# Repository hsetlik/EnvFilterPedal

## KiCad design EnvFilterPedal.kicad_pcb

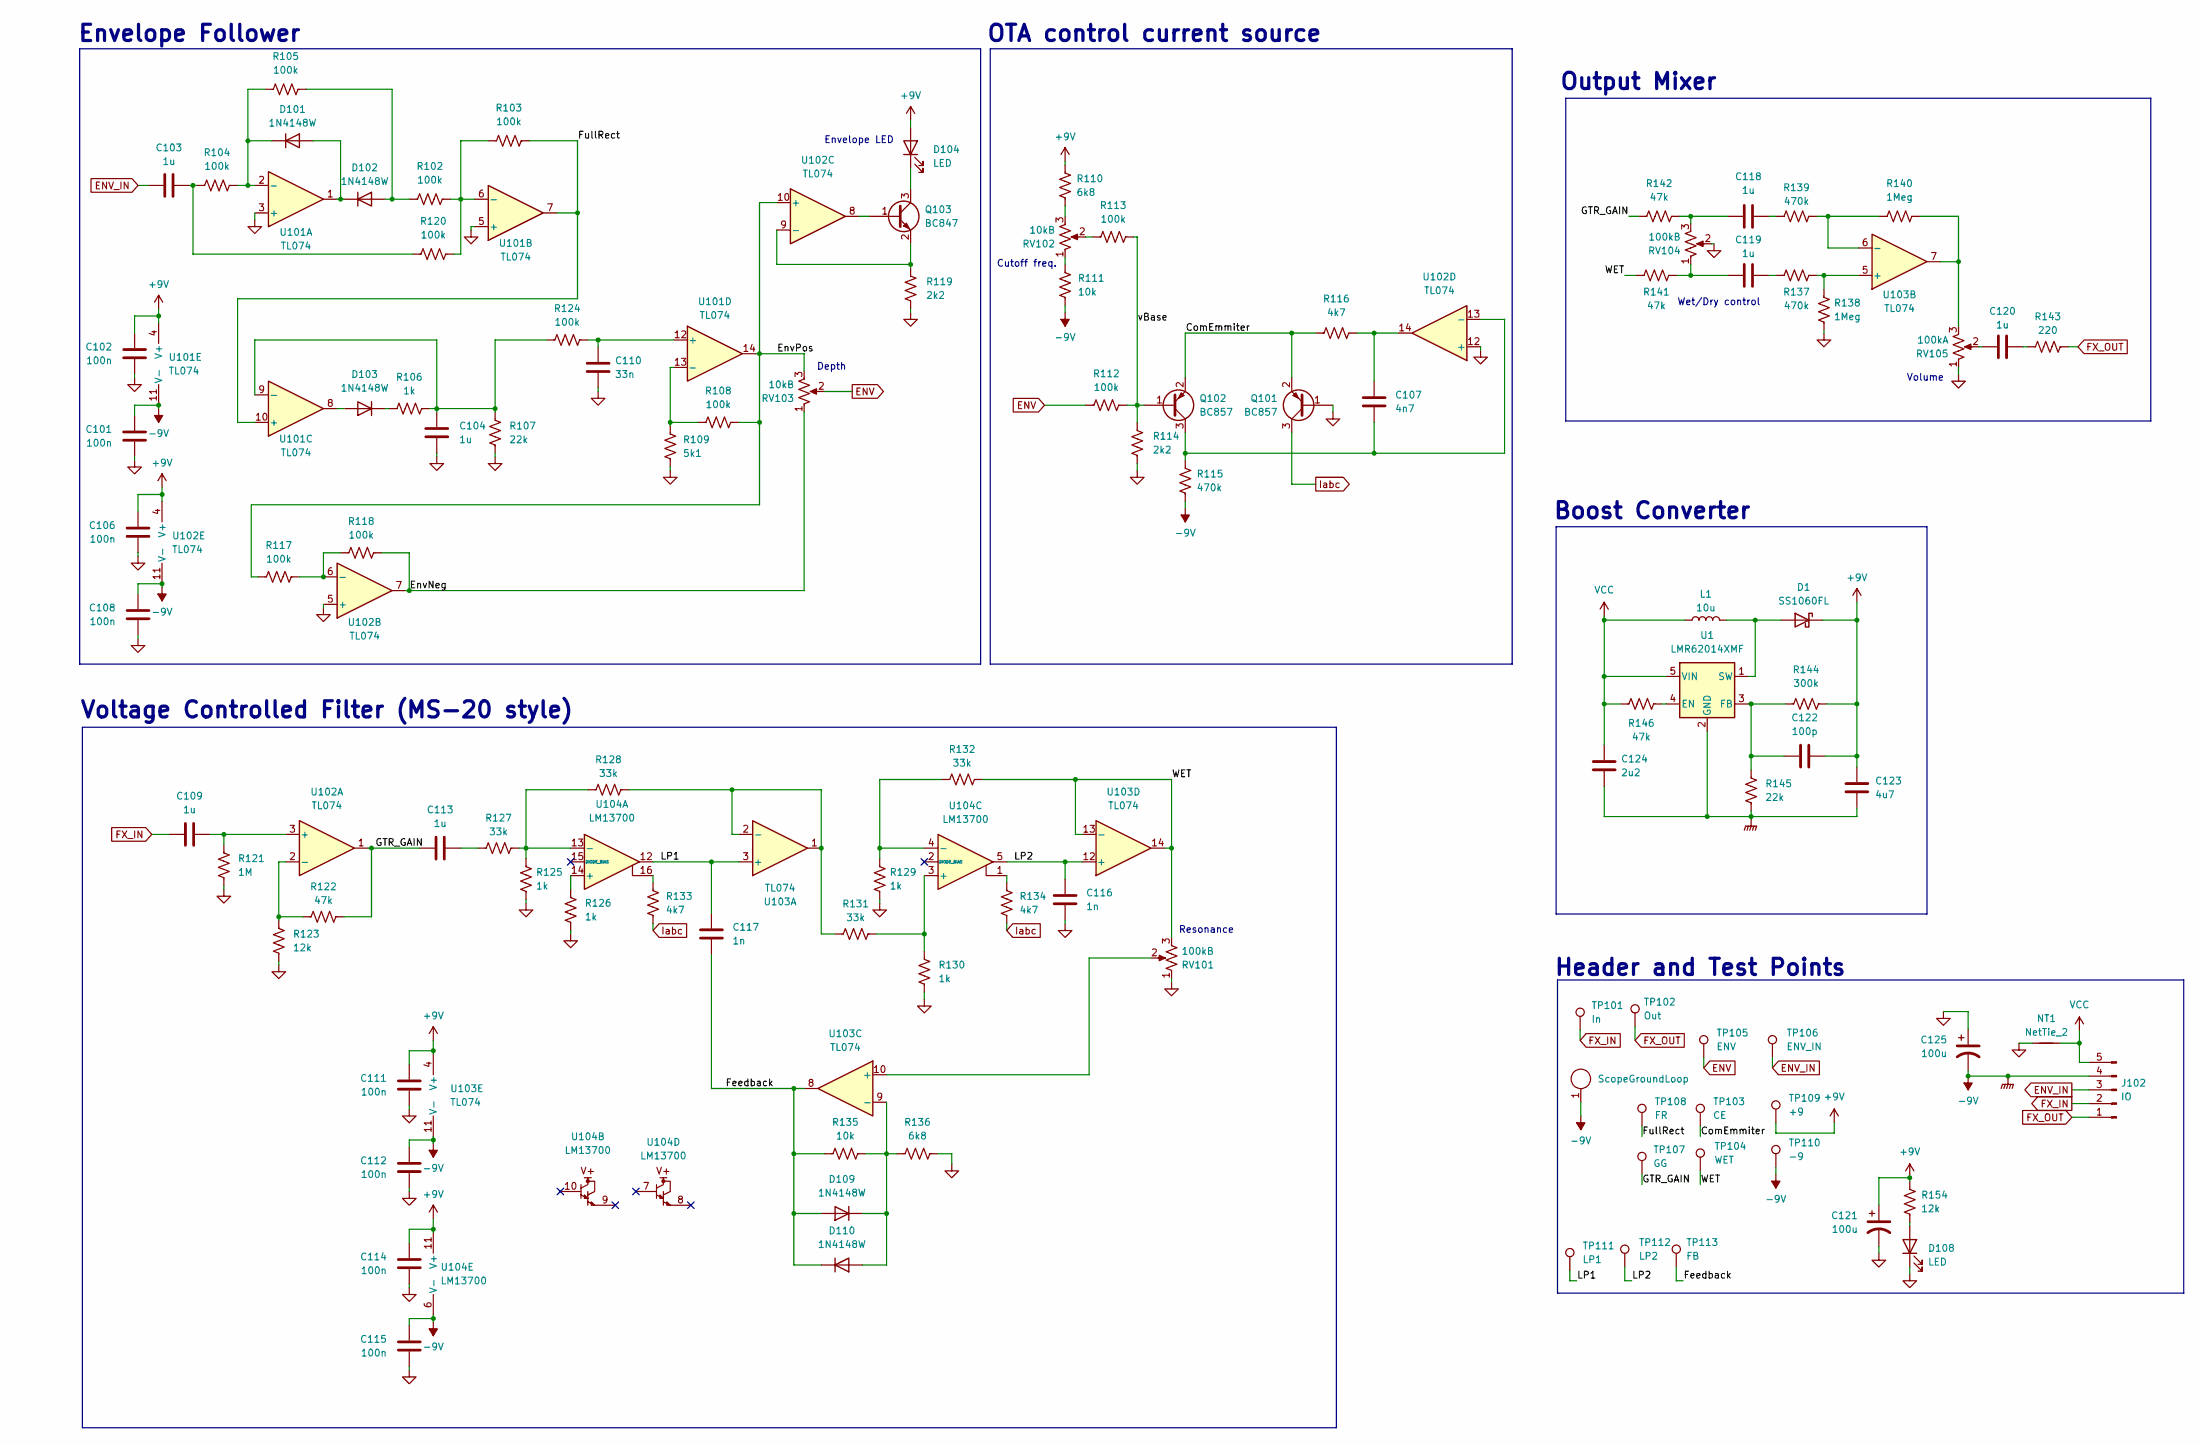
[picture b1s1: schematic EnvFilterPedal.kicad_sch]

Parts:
C101, C102, C106, C108, C111, C112, C114, C115: 100n; C_0805_2012Metric
C103, C104, C109, C113, C118, C119, C120: 1u; C_0805_2012Metric
C107: 4n7; C_0805_2012Metric
C110: 33n; C_0805_2012Metric
C116, C117: 1n; C_0805_2012Metric
C121, C125: 100u; CP_Radial_D5.0mm_P2.00mm
C122: 100p; C_0805_2012Metric
C123: 4u7; C_0805_2012Metric
C124: 2u2; C_0805_2012Metric
D1: SS1060FL; D_SOD-123F
D101, D102, D103, D109, D110: 1N4148W; D_SOD-123
D104, D108: LED; LED_D3.0mm
J101: ScopeGroundLoop; THT_GND_WIRE
J102: IO; PinHeader_1x05_P2.54mm_Vertical
L1: 10u; L_SigTransformer_SLPPI04_15
NT1: NetTie_2; NetTie-2_SMD_Pad0.5mm
Q101, Q102: BC857; SOT-23
Q103: BC847; SOT-23
R102, R103, R104, R105, R108, R112, R113, R117, R118, R120, R124: 100k; R_0805_2012Metric
R106, R125, R126, R129, R130: 1k; R_0805_2012Metric
R107, R145: 22k; R_0805_2012Metric
R109: 5k1; R_0805_2012Metric
R110, R136: 6k8; R_0805_2012Metric
R111, R135: 10k; R_0805_2012Metric
R114, R119: 2k2; R_0805_2012Metric
R115, R137, R139: 470k; R_0805_2012Metric
R116, R133, R134: 4k7; R_0805_2012Metric
R121: 1M; R_0805_2012Metric
R122, R141, R142, R146: 47k; R_0805_2012Metric
R123, R154: 12k; R_0805_2012Metric
R127, R128, R131, R132: 33k; R_0805_2012Metric
R138, R140: 1Meg; R_0805_2012Metric
R143: 220; R_0805_2012Metric
R144: 300k; R_0805_2012Metric
RV101, RV104: 100kB; Potentiometer_Alpha_RV16AF_42_VeryLong
RV102, RV103: 10kB; Potentiometer_Alpha_RV16AF_42_VeryLong
RV105: 100kA; Potentiometer_Alpha_RV16AF_42_VeryLong
TP101: In; TestPoint_THTPad_D2.0mm_Drill1.0mm_VAL
TP102: Out; TestPoint_THTPad_D2.0mm_Drill1.0mm_VAL
TP103: CE; TestPoint_THTPad_D2.0mm_Drill1.0mm_VAL
TP104: WET; TestPoint_THTPad_D2.0mm_Drill1.0mm_VAL
TP105: ENV; TestPoint_THTPad_D2.0mm_Drill1.0mm_VAL
TP106: ENV_IN; TestPoint_THTPad_D2.0mm_Drill1.0mm_VAL
TP107: GG; TestPoint_THTPad_D2.0mm_Drill1.0mm_VAL
TP108: FR; TestPoint_THTPad_D2.0mm_Drill1.0mm_VAL
TP109: +9; TestPoint_THTPad_D2.0mm_Drill1.0mm_VAL
TP110: -9; TestPoint_THTPad_D2.0mm_Drill1.0mm_VAL
TP111: LP1; TestPoint_THTPad_D2.0mm_Drill1.0mm_VAL
TP112: LP2; TestPoint_THTPad_D2.0mm_Drill1.0mm_VAL
TP113: FB; TestPoint_THTPad_D2.0mm_Drill1.0mm_VAL
U1: LMR62014XMF; SOT-23-5
U101, U102, U103: TL074; SOIC-14_3.9x8.7mm_P1.27mm
U104: LM13700; SOIC-16_3.9x9.9mm_P1.27mm

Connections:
+9V: C102.1, C106.1, C111.1, C114.1, C121.1, C122.2, C123.1, D1.1 (K), D104.2 (A), R110.1, R144.2, R154.1, TP109.1 (1_1), U101.4 (V+), U102.4 (V+), U103.4 (V+), U104.11 (V+)
-9V: C101.1, C108.1, C112.1, C115.1, C123.2, C124.2, C125.2, J101.1, J102.4, R111.2, R115.2, R145.1, TP110.1 (1_1), U1.2 (GND), U101.11 (V-), U102.11 (V-), U103.11 (V-), U104.6 (V-)
/ComEmmiter: Q101.2 (E), Q102.2 (E), R116.1, TP103.1 (1_1)
/EnvNeg: R118.2, RV103.1, U102.7
/EnvPos: R108.2, R117.1, RV103.3, U101.14, U102.10 (+)
/Feedback: C117.2, D109.2 (A), D110.1 (K), R135.1, TP113.1 (1_1), U103.8
/FullRect: R103.2, TP108.1 (1_1), U101.7, U101.10 (+)
/GTR_GAIN: C113.1, R122.2, R142.1, TP107.1 (1_1), U102.1
/LP1: C117.1, TP111.1 (1_1), U103.3 (+), U104.12
/LP2: C116.1, TP112.1 (1_1), U103.12 (+), U104.5
/WET: R132.2, R141.1, RV101.3, TP104.1 (1_1), U103.13 (-), U103.14
/vBase: Q102.1 (B), R112.2, R113.2, R114.1
ENV: R112.1, RV103.2, TP105.1 (1_1)
ENV_IN: C103.1, J102.3, TP106.1 (1_1)
FX_IN: C109.1, J102.2, TP101.1 (1_1)
FX_OUT: J102.1, R143.2, TP102.1 (1_1)
GND: C101.2, C102.2, C104.2, C106.2, C108.2, C110.2, C111.2, C112.2, C114.2, C115.2, C116.2, C121.2, C125.1, D108.1 (K), NT1.1, Q101.1 (B), R107.2, R109.2, R114.2, R119.2, R121.2, R123.2, R125.1, R126.1, R129.1, R130.1, R136.1, R138.2, RV101.1, RV104.2, RV105.1, U101.3 (+), U101.5 (+), U102.5 (+), U102.12 (+)
Iabc: Q101.3 (C), R133.1, R134.1
unnamed: C103.2, R104.1, R120.1
unnamed: C107.1, R116.2, U102.14
unnamed: C113.2, R127.1
unnamed: C118.1, R142.2, RV104.3
unnamed: C118.2, R139.1
unnamed: C119.1, R141.2, RV104.1
unnamed: C119.2, R137.1
unnamed: C120.1, R143.1
unnamed: C120.2, RV105.2
unnamed: D1.2 (A), L1.2, U1.1 (SW)
unnamed: D101.2 (A), D102.1 (K), U101.1
unnamed: D101.1 (K), R104.2, R105.1, U101.2 (-)
unnamed: D102.2 (A), R102.1, R105.2
unnamed: D103.2 (A), U101.8
unnamed: D103.1 (K), R106.1
unnamed: D104.1 (K), Q103.3 (C)
unnamed: D108.2 (A), R154.2
unnamed: D109.1 (K), D110.2 (A), R135.2, R136.2, U103.9 (-)
unnamed: C107.2, Q102.3 (C), R115.1, U102.13 (-)
unnamed: Q103.1 (B), U102.8
unnamed: Q103.2 (E), R119.1, U102.9 (-)
unnamed: R110.2, RV102.3
unnamed: R111.1, RV102.1
unnamed: R113.1, RV102.2
unnamed: R133.2, U104.16
unnamed: R134.2, U104.1
unnamed: R140.2, RV105.3, U103.7
unnamed: R146.2, U1.4 (EN)
unnamed: C122.1, R144.1, R145.2, U1.3 (FB)
unnamed: R102.2, R103.1, R120.2, U101.6 (-)
unnamed: C104.1, R106.2, R107.1, R124.1, U101.9 (-)
unnamed: C110.1, R124.2, U101.12 (+)
unnamed: R108.1, R109.1, U101.13 (-)
unnamed: C109.2, R121.1, U102.3 (+)
unnamed: R122.1, R123.1, U102.2 (-)
unnamed: R117.2, R118.1, U102.6 (-)
unnamed: R128.2, R131.1, U103.1, U103.2 (-)
unnamed: R137.2, R138.1, U103.5 (+)
unnamed: R139.2, R140.1, U103.6 (-)
unnamed: RV101.2, U103.10 (+)
unnamed: R126.2, U104.14 (+)
unnamed: R125.2, R127.2, R128.1, U104.13 (-)
unnamed: R130.2, R131.2, U104.3 (+)
unnamed: R129.2, R132.1, U104.4 (-)
VCC: C124.1, J102.5, L1.1, NT1.2, R146.1, U1.5 (VIN)

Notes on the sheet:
Volume
Depth
Cutoff freq.
Boost Converter
Envelope Follower
Output Mixer
Resonance
Wet/Dry control
Header and Test Points
Envelope LED
Voltage Controlled Filter (MS-20 style)
OTA control current source

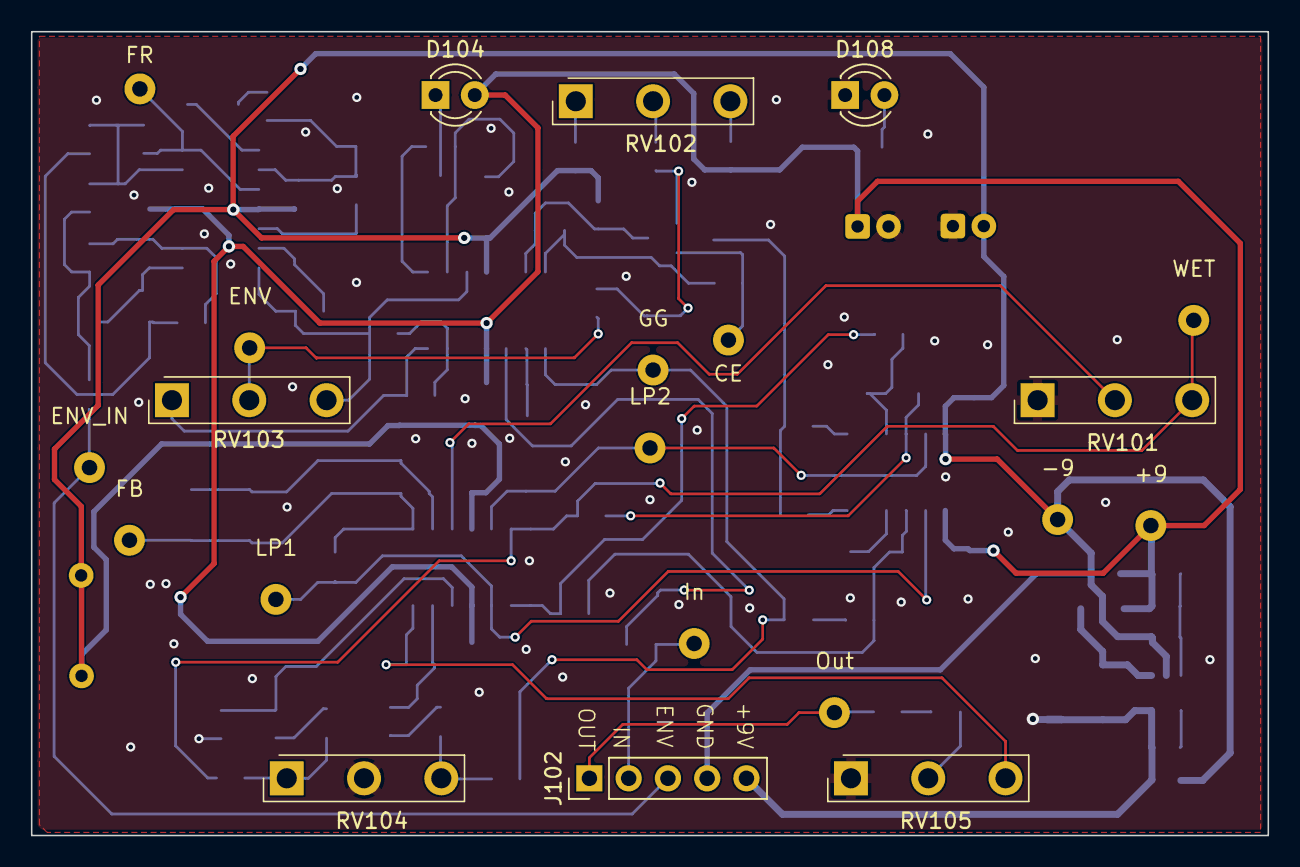
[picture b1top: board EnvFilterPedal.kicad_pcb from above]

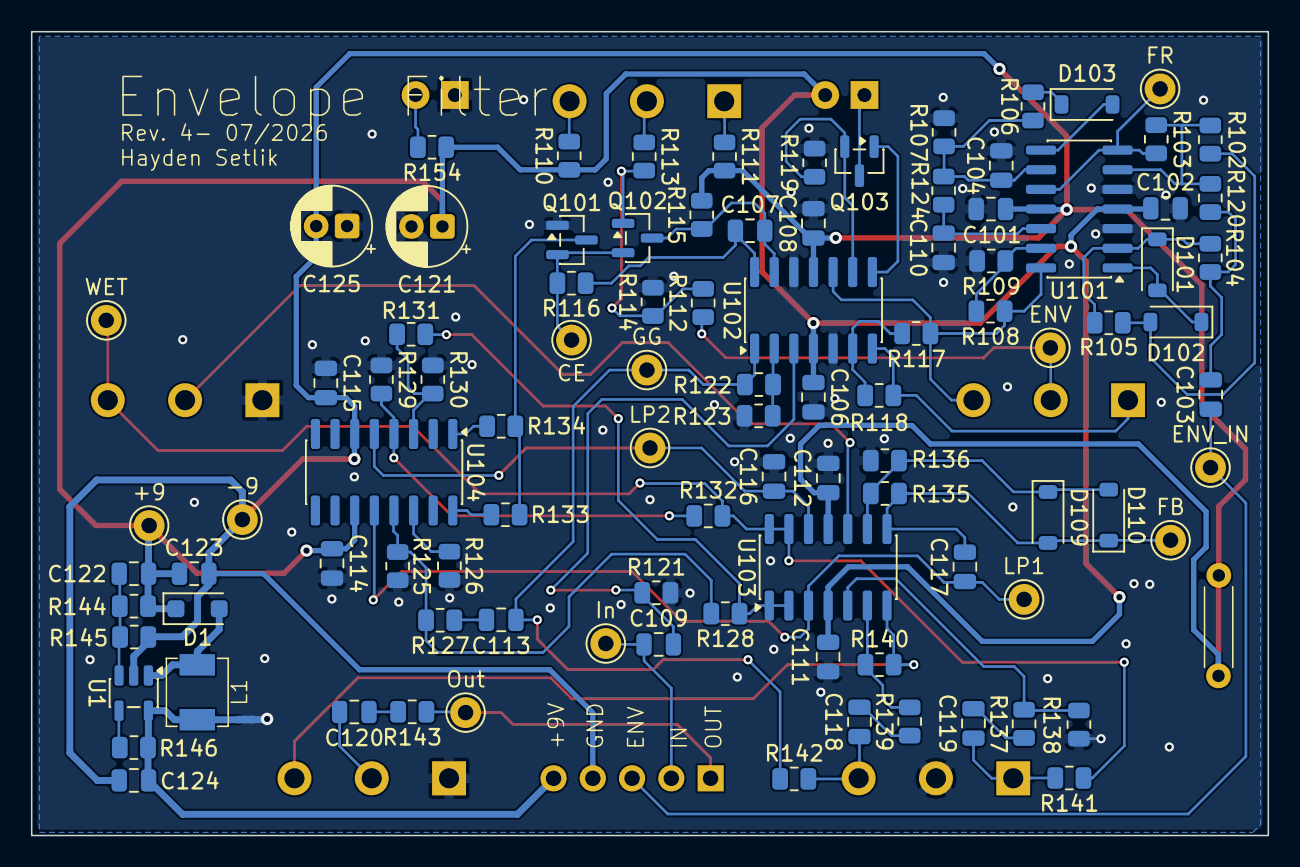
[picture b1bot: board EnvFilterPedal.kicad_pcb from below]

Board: 4 copper layers, 80.0 x 52.0 mm, 108 parts (100 on the bottom side), 63 nets.

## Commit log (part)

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2024-12-23 schem and simulation for env follower
2024-12-24 schematic 1st pass
2024-12-24 footprints assigned
2025-01-10 rev 1 gerber
2025-01-18 filter value tweaks
2025-01-19 rev2 simulation stuff
2025-01-19 rev2 schematic and footprints
2025-01-20 4 layer layout
2025-01-20 routed, DRC passing
2025-01-21 MCU pinout schematic
2025-01-21 cleaned up routing
2025-01-24 rev2 gerber
2025-01-24 added BOM
2025-01-24 enclosure SVG files
2025-01-28 simulation for single supply ladder filter
2025-01-28 discrete current source sim
2025-02-07 component tweaks after playing thru it for a day
2025-02-07 minor value tweaks
2025-02-12 added SMPS input filtering
2025-02-12 rev3 sent to fab
2026-03-10 switched to 1u inductor on SMPS output
2026-03-10 laid out new inductor, some trace cleanup
2026-03-14 smps simulation in LTSpice
2026-03-14 vaues for LC power filter
2026-03-15 new layout
2026-03-16 stitching vias, minor layout changes
2026-03-16 rev4 sent to fab
